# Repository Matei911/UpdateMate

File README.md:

# UpdateMate

**UpdateMate** is an open-source, low-power ePaper tablet designed for tinkerers, developers, and DIY enthusiasts.  
Built around the ESP32 microcontroller, it offers a customizable platform for displaying relevant, distraction-free information — from weather forecasts and calendar events to news, sensor data, and more.

## Preview

<table>
  <tr>
    <td align="center"><br/><sub>3D View of Tablet</sub></td>
    <td align="center"><br/><sub>3D View of PCB</sub></td>
  </tr>
  <tr>
    <td align="center"><br/><sub>Exploded View (Top)</sub></td>
    <td align="center"><br/><sub>Exploded View (Bottom)</sub></td>
  </tr>
</table>

## Features

- 🖥️ 7.5-inch black-and-white ePaper display from Waveshare  
- ⚡ Low power consumption with deep sleep support  
- 🧩 Rich peripheral support: sensors, SD card, RTC, fuel gauge, and more  
- 🔧 Designed for customization: easily add your own widgets, components, or software

## Ideal for

- 📖 eBook and tablet replacements  
- 🏡 Smart home dashboards  
- 🌦️ Always-on weather/news displays  
- 📅 Personal productivity boards  
- 📡 IoT project front-ends  
- 🧪 Educational embedded systems kits

## Bill of Materials (BoM)

The main components in the tablet

| Component               | Interface | Description                                 | Link |
|------------------------|-----------|---------------------------------------------|------|
| **ESP32-C6-WROOM-1-N4**| MCU       | Main microcontroller                        | [Mouser](https://eu.mouser.com/ProductDetail/Espressif-Systems/ESP32-C6-WROOM-1-N4?qs=8Wlm6%252BaMh8R1JRAtXlt87w%3D%3D) |
| **7.5" Waveshare ePaper** | SPI    | Black-and-white e-paper display             | [Waveshare](https://www.waveshare.com/7.5inch-e-paper.htm) |
| **MicroSD Card Socket** | SPI       | For storage and data logging                | [TME](https://www.tme.eu/ro/details/mcc-sdmicro/conectori-pentru-cartele/attend/112a-taar-r03/?utm_source=google&utm_medium=cpc&utm_campaign=RUMUNIA%20%5BP%5D%5BDC%5D&gad_source=1&gad_campaignid=8175080604&gbraid=0AAAAADyylhKvBZhJjt9PiCTA7ccHCAagN&gclid=Cj0KCQjw-NfDBhDyARIsAD-ILeD5bqtRTQDJJ5KzH339OMhsTZl5OwnY6A_-zTqHLYSh2y26Atg0Cr8aAshjEALw_wcB&gclsrc=aw.ds) |
| **W25Q512JVEIQ NOR Flash** | SPI  | 64 MB external flash memory                 | [Mouser](https://eu.mouser.com/ProductDetail/Winbond/W25Q512JVEIQ?qs=l7cgNqFNU1jw6svr3at6tA%3D%3D) |
| **MAX17048 Fuel Gauge** | I2C       | Battery voltage and state-of-charge monitor | [Mouser](https://eu.mouser.com/ProductDetail/Analog-Devices-Maxim-Integrated/MAX17048G%2bT10?qs=D7PJwyCwLAoGnnn8jEPRBQ%3D%3D) |
| **BME680 Sensor Board** | I2C       | Environmental sensor (temp, humidity, gas)  | [Mouser](https://eu.mouser.com/ProductDetail/Bosch-Sensortec/BME680-Shuttle-Board-3.0?qs=Wj%2FVkw3K%252BMABg5lm5143Ww%3D%3D) |
| **DS3231SN RTC**        | I2C       | Real-time clock with temperature compensation | [Mouser](https://eu.mouser.com/ProductDetail/Analog-Devices-Maxim-Integrated/DS3231SN?qs=1eQvB6Dk1vhUlr8%2FOrV0Fw%3D%3D&utm_id=20109199409&utm_source=google&utm_medium=cpc&utm_marketing_tactic=emeacorp&gad_source=1&gad_campaignid=20109199409&gbraid=0AAAAADn_wf2OPp6JmRENVY2T7SRbqdMYH&gclid=Cj0KCQjw-NfDBhDyARIsAD-ILeBzHcIxR8KDbRAJnh_ZM7th9YkG_cXsf5fStQOxZy3EcUWmKn77gJcaAmQ9EALw_wcB) |

## Gallery

Pictures with the features already implemented on the tablet.

<table>
  <tr>
    <td align="center">
      <br/>
      <sub>Main Page View</sub>
    </td>
    <td align="center">
      <br/>
      <sub>eBook Page View</sub>
    </td>
    <td align="center">
      <br/>
      <sub>Stock Page View</sub>
    </td>
  </tr>
  <tr>
    <td align="center">
      <br/>
      <sub>News Page View</sub>
    </td>
    <td align="center">
      <br/>
      <sub>App Launcher View</sub>
    </td>
    <td align="center">
      <br/>
      <sub>PCB inside case</sub>
    </td>
  </tr>
</table>

## Contents

The repository is structured into two main sections:

### `/hardware`
- Autodesk Fusion 360 design files for the custom PCB  
- 3D model files for the full tablet case, including STL/STEP formats for printing or editing  
- Schematics and layout files for manufacturing the board

### `/software`
- Arduino sketches for individual components (e.g. display, sensors, Wi-Fi, etc.) for testing  
- Full firmware implementation for the UpdateMate tablet, enabling all features shown in the gallery (weather, news, stocks, calendar, eBooks)

**Enjoy tinkering!**

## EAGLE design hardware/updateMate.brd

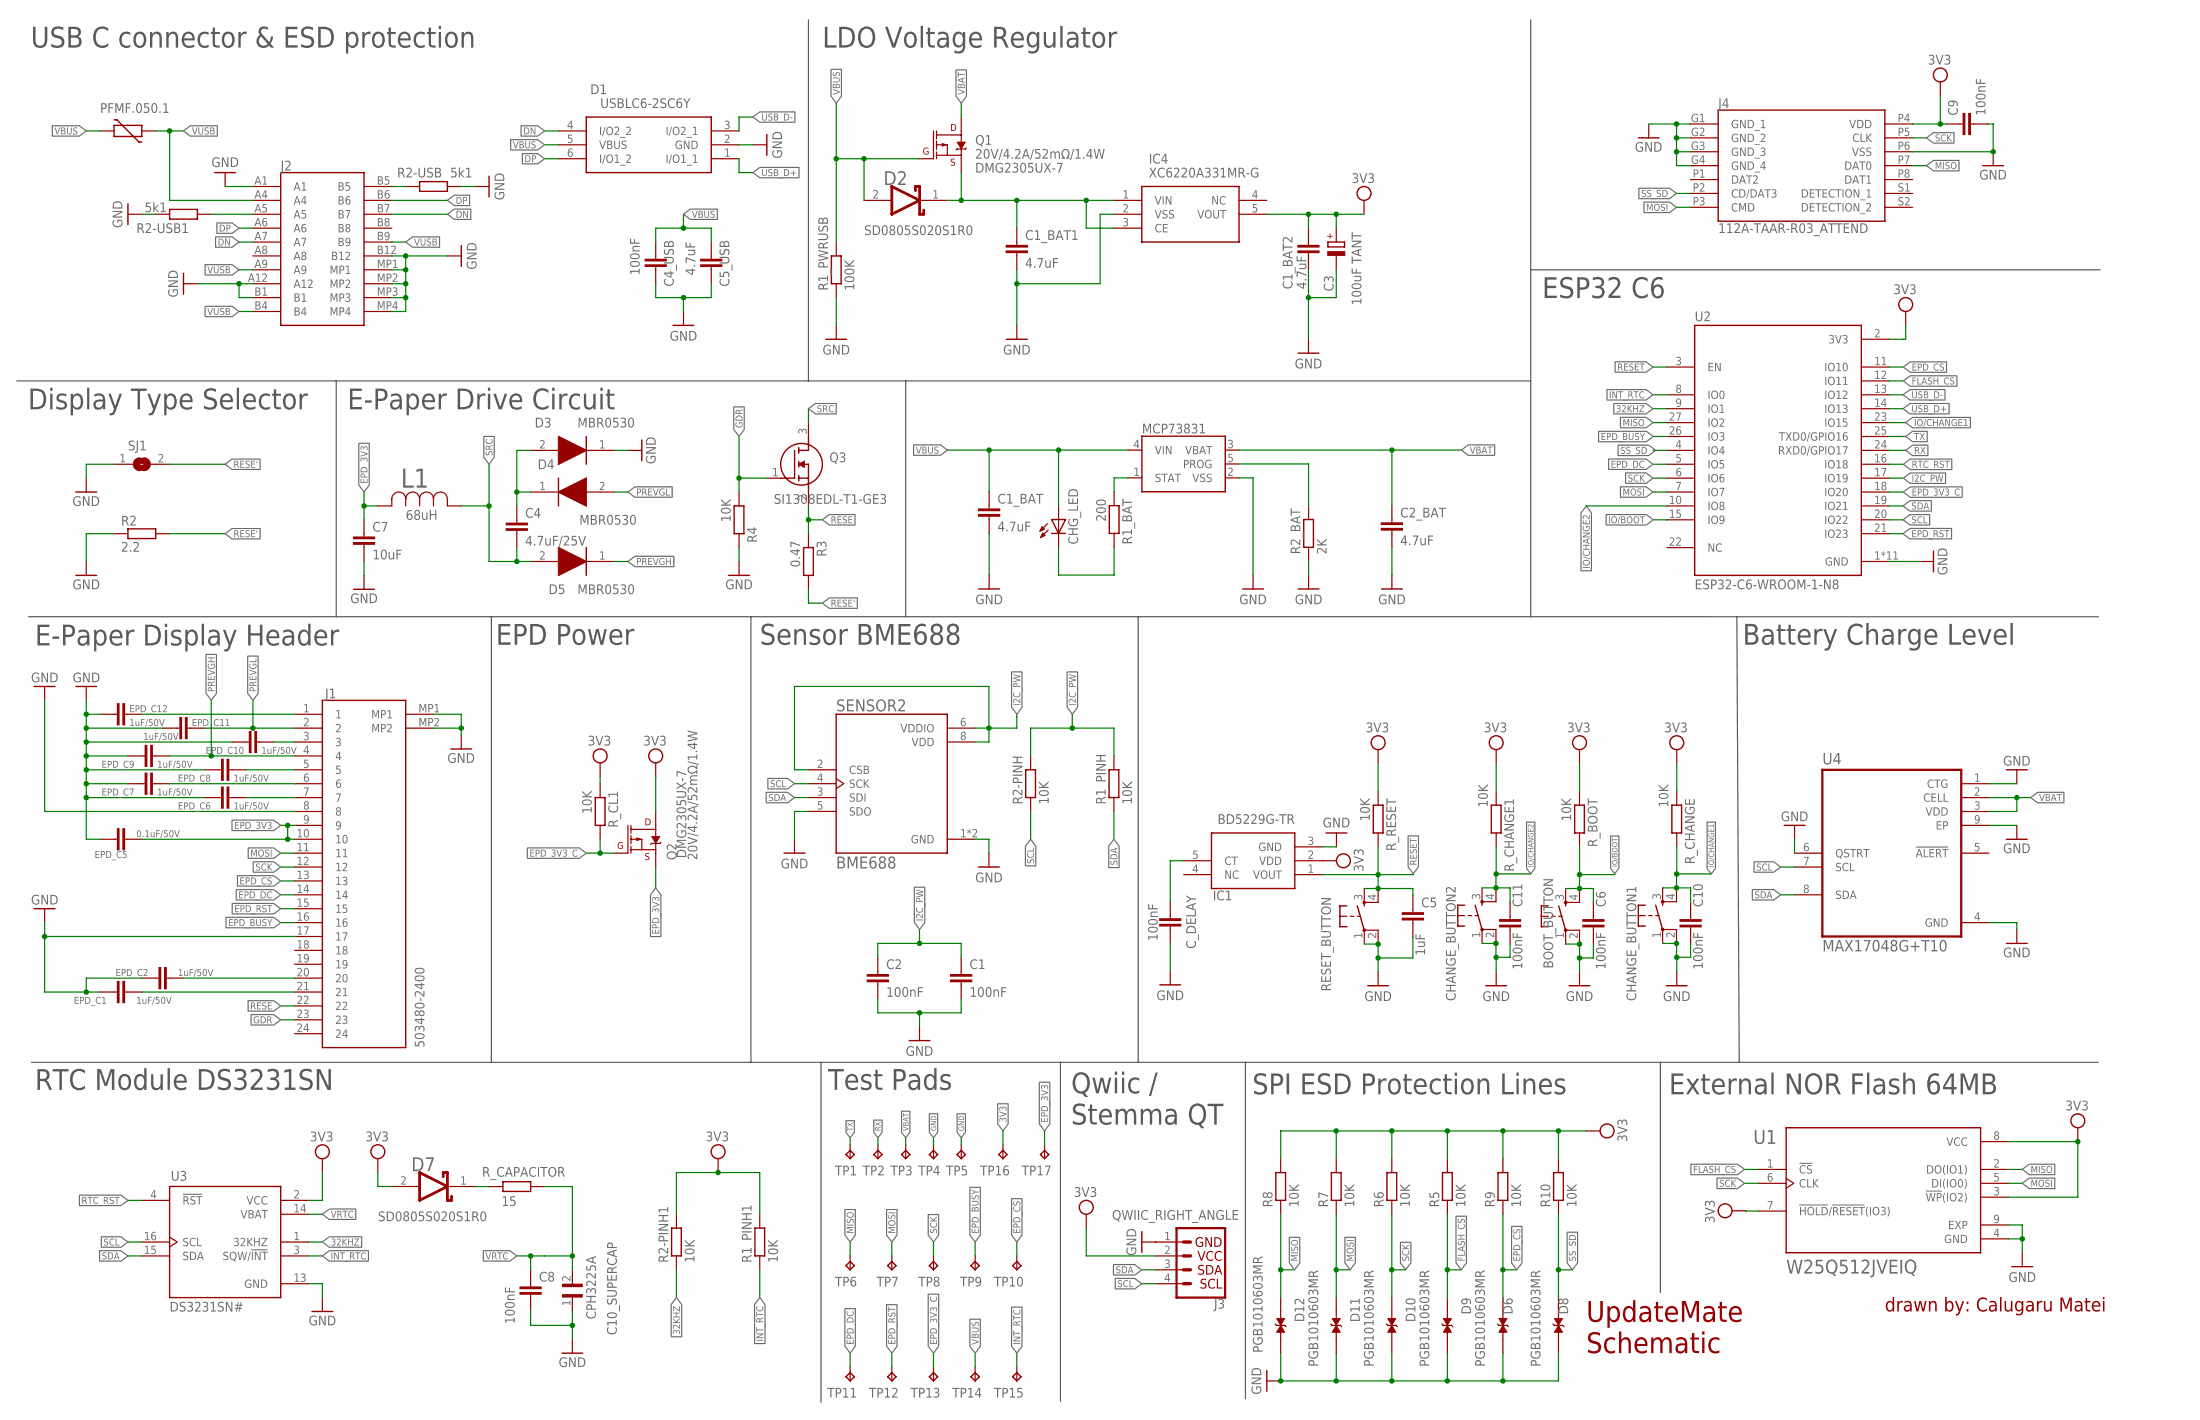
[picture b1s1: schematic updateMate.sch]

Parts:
BOOT_BUTTON: BUTTON_CUSYOMV1; MYBUTTON
C1, C2, C4_USB, C6, C8, C10, C11: 100nF; ESP32_WROVER_EAGLE-LTSPICE_C0402
C1_BAT, C1_BAT1, C1_BAT2, C2_BAT, C5_USB: 4.7uF; ESP32_WROVER_EAGLE-LTSPICE_C0402
C3: 100uF TANT; RCL_CT3528
C4: 4.7uF/25V; ESP32_WROVER_EAGLE-LTSPICE_C0402
C5: 1uF; ESP32_WROVER_EAGLE-LTSPICE_C0402
C7: 10uF; ESP32_WROVER_EAGLE-LTSPICE_C0402
C9: 100nF; EAGLE-LTSPICE_C0402
C10_SUPERCAP: CPH3225A; CAPCP3225X100N
CHANGE_BUTTON1, CHANGE_BUTTON2: BUTTON_CUSYOMV1; MYBUTTON
CHG_LED: ADAFRUIT_LEDCHIP-LED0603; ADAFRUIT_CHIP-LED0603
C_DELAY: 100nF; ESP32_WROVER_EAGLE-LTSPICE_C0402
D1: USBLC6-2SC6Y; SOT95P280X145-6N
D2: ESP32_WROVER_AVX---SD0805S020S1R0_AVX_SD0805S020S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; ESP32_WROVER_AVX---SD0805S020S1R0_AVX_SD0805S020S1R0_0
D3, D4, D5: MBR0530; SOD3716X135N
D6, D8, D9, D10, D11, D12: PGB1010603MR; DIOC1608X36N
D7: SD0805S020S1R0; ESP32_WROVER_AVX---SD0805S020S1R0_AVX_SD0805S020S1R0_0
EPD_C1, EPD_C2, EPD_C6, EPD_C7, EPD_C8, EPD_C9, EPD_C10, EPD_C11, EPD_C12: 1uF/50V; ESP32_WROVER_EAGLE-LTSPICE_C0402
EPD_C5: 0.1uF/50V; ESP32_WROVER_EAGLE-LTSPICE_C0402
IC1: BD5229G-TR; SOT95P280X125-5N
IC4: XC6220A331MR-G; SOT95P280X120-5N
J1: 503480-2400; 5034802400
J2: SAMACSYS_PARTS_USB4110-GF-A; SAMACSYS_PARTS_USB4110GFA
J3: QWIIC_RIGHT_ANGLE; JST04_1MM_RA
J4: 112A-TAAR-R03_ATTEND; 112ATAARR03ATTEND
L1: 68uH; IND_4828-WE-TPC_WRE
MCP73831: ESP32_WROVER_SPARKFUN-IC-POWER_MCP73831; ESP32_WROVER_SPARKFUN-IC-POWER_SOT23-5
PFMF.050.1: ESP32C6_VARISTORCN1812; ESP32C6_VARISTOR_CT/CN1812
Q1, Q2: 20V/4.2A/52mΩ/1.4W; ESP32_WROVER_SPARKFUN-DISCRETESEMI_SOT23-3
Q3: SI1308EDL-T1-GE3; SOT65P210X110-3N
R1_BAT: 200; ESP32_WROVER_EAGLE-LTSPICE_R0402
R1_PINH, R1_PINH1, R2-PINH, R2-PINH1, R4, R5, R6, R7, R8, R9, R10: 10K; ESP32_WROVER_EAGLE-LTSPICE_R0402
R1_PWRUSB: 100K; ESP32_WROVER_EAGLE-LTSPICE_R0402
R2: 2.2; ESP32_WROVER_EAGLE-LTSPICE_R0402
R2-USB, R2-USB1: 5k1; ESP32_WROVER_EAGLE-LTSPICE_R0402
R2_BAT: 2K; ESP32_WROVER_EAGLE-LTSPICE_R0402
R3: 0.47; ESP32_WROVER_EAGLE-LTSPICE_R0402
RESET_BUTTON: BUTTON_CUSYOMV1; MYBUTTON
R_BOOT: 10K; ESP32_WROVER_EAGLE-LTSPICE_R0402
R_CAPACITOR: 15; ESP32_WROVER_EAGLE-LTSPICE_R0402
R_CHANGE, R_CHANGE1: 10K; ESP32_WROVER_EAGLE-LTSPICE_R0402
R_CL1: 10K; ESP32_WROVER_EAGLE-LTSPICE_R0402
R_RESET: 10K; ESP32_WROVER_EAGLE-LTSPICE_R0402
SENSOR2: BME688; ESP32_WROVER_BME680_PSON80P300X300X100-8N
SJ1: SJ
TP1, TP2, TP3, TP4, TP5, TP6, TP7, TP8, TP9, TP10, TP11, TP12, TP13, TP14, TP15, TP16, TP17: TPTP20R; TP20R
U1: W25Q512JVEIQ; SON127P600X800X80-9N
U2: ESP32-C6-WROOM-1-N8; XCVR_ESP32-C6-WROOM-1-N8
U3: DS3231SN#; SOIC127P1032X265-16N
U4: MAX17048G+T10; SON50P200X200X80-9N

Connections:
3V3: C1_BAT2.1, C3.+, C9.1, D7.2 (ANODE), IC1.2 (VDD), IC4.5 (VOUT), J3.2, J4.P4 (VDD), Q2.3 (D), R1_PINH1.2, R2-PINH1.2, R5.2, R6.2, R7.2, R8.2, R9.2, R10.2, R_BOOT.1, R_CHANGE.1, R_CHANGE1.1, R_CL1.1, R_RESET.1, TP16.TP, U1.3 (!WP!(IO2)), U1.7 (!HOLD!/!RESET!(IO3)), U1.8 (VCC), U2.2 (3V3), U3.2 (VCC)
32KHZ: R2-PINH1.1, U2.9 (IO1), U3.1 (32KHZ)
DN: D1.4 (I/O2_2), J2.A7, J2.B7
DP: D1.6 (I/O1_2), J2.A6, J2.B6
EPD_3V3: C7.1, EPD_C5.1, J1.9, J1.10, L1.2, Q2.2 (S), TP17.TP
EPD_3V3_C: Q2.1 (G), R_CL1.2, TP13.TP, U2.18 (IO20)
EPD_BUSY: J1.16, TP9.TP, U2.26 (IO3)
EPD_CS: D6.1, J1.13, R9.1, TP10.TP, U2.11 (IO10)
EPD_DC: J1.14, TP11.TP, U2.5 (IO5)
EPD_RST: J1.15, TP12.TP, U2.21 (IO23)
FLASH_CS: D9.1, R5.1, U1.1 (!CS), U2.12 (IO11)
GDR: J1.23, Q3.1 (G), R4.1
GND: BOOT_BUTTON.1, BOOT_BUTTON.2, C1.2, C1_BAT.2, C1_BAT1.2, C1_BAT2.2, C2.2, C2_BAT.2, C3.-, C4_USB.2, C5.2, C5_USB.2, C6.2, C7.2, C8.2, C9.2, C10.2, C10_SUPERCAP.1, C11.2, CHANGE_BUTTON1.1, CHANGE_BUTTON1.2, CHANGE_BUTTON2.1, CHANGE_BUTTON2.2, C_DELAY.2, D1.2 (GND), D3.1 (K), D6.2, D8.2, D9.2, D10.2, D11.2, D12.2, EPD_C1.2, EPD_C2.2, EPD_C5.2, EPD_C6.2, EPD_C7.2, EPD_C8.2, EPD_C9.2, EPD_C10.2, EPD_C11.2, EPD_C12.2, IC1.3 (GND), IC4.2 (VSS), J1.8, J1.17, J1.MP1, J1.MP2, J2.A1, J2.A12, J2.B1, J2.B12, J2.MP1, J2.MP2, J2.MP3, J2.MP4, J3.1, J4.G1 (GND_1), J4.G2 (GND_2), J4.G3 (GND_3), J4.G4 (GND_4), J4.P6 (VSS), MCP73831.2 (VSS), R1_PWRUSB.1, R2.1, R2-USB.2, R2-USB1.1, R2_BAT.1, R4.2, RESET_BUTTON.1, RESET_BUTTON.2, SENSOR2.1 (GND), SENSOR2.5 (SDO), SENSOR2.7 (GND), SJ1.1, TP4.TP, TP5.TP, U1.4 (GND), U1.9 (EXP), U2.1 (GND), U2.28 (GND), U2.29_1 (GND), U2.29_2 (GND), U2.29_3 (GND), U2.29_4 (GND), U2.29_5 (GND), U2.29_6 (GND), U2.29_7 (GND), U2.29_8 (GND), U2.29_9 (GND), U3.13 (GND), U4.1 (CTG), U4.4 (GND), U4.6 (QSTRT), U4.9 (EP)
I2C_PW: C1.1, C2.1, R1_PINH.2, R2-PINH.2, SENSOR2.2 (CSB), SENSOR2.6 (VDDIO), SENSOR2.8 (VDD), U2.17 (IO19)
INT_RTC: R1_PINH1.1, TP15.TP, U2.8 (IO0), U3.3 (SQW/!INT)
IO/BOOT: BOOT_BUTTON.3, BOOT_BUTTON.4, C6.1, R_BOOT.2, U2.15 (IO9)
IO/CHANGE1: C10.1, CHANGE_BUTTON1.3, CHANGE_BUTTON1.4, R_CHANGE.2, U2.23 (IO15)
IO/CHANGE2: C11.1, CHANGE_BUTTON2.3, CHANGE_BUTTON2.4, R_CHANGE1.2, U2.10 (IO8)
MISO: D12.1, J4.P7 (DAT0), R8.1, TP6.TP, U1.2 (DO(IO1)), U2.27 (IO2)
MOSI: D11.1, J1.11, J4.P3 (CMD), R7.1, TP7.TP, U1.5 (DI(IO0)), U2.7 (IO7)
unnamed: J2.B5, R2-USB.1
unnamed: C_DELAY.1, IC1.5 (CT)
unnamed: C1_BAT1.1, D2.1 (CATHODE), IC4.1 (VIN), IC4.3 (CE), Q1.2 (S)
unnamed: J2.A5, R2-USB1.2
unnamed: D7.1 (CATHODE), R_CAPACITOR.2
unnamed: EPD_C1.1, J1.21
unnamed: EPD_C2.1, J1.20
unnamed: C4.1, D3.2 (A), D4.1 (K)
unnamed: MCP73831.5 (PROG), R2_BAT.2
unnamed: MCP73831.1 (STAT), R1_BAT.1
unnamed: CHG_LED.C, R1_BAT.2
unnamed: EPD_C6.1, J1.7
unnamed: EPD_C7.1, J1.6
unnamed: EPD_C8.1, J1.5
unnamed: EPD_C10.1, J1.3
unnamed: EPD_C12.1, J1.1
PREVGH: D5.1 (K), EPD_C9.1, J1.4
PREVGL: D4.2 (A), EPD_C11.1, J1.2
RESE: J1.22, Q3.2 (S), R3.1
RESE': R2.2, R3.2, SJ1.2
RESET: C5.1, IC1.1 (VOUT), RESET_BUTTON.3, RESET_BUTTON.4, R_RESET.2, U2.3 (EN)
RTC_RST: U2.16 (IO18), U3.4 (!RST)
RX: TP2.TP, U2.24 (RXD0/GPIO17)
SCK: D10.1, J1.12, J4.P5 (CLK), R6.1, TP8.TP, U1.6 (CLK), U2.6 (IO6)
SCL: J3.4, R2-PINH.1, SENSOR2.4 (SCK), U2.20 (IO22), U3.16 (SCL), U4.7 (SCL)
SDA: J3.3, R1_PINH.1, SENSOR2.3 (SDI), U2.19 (IO21), U3.15 (SDA), U4.8 (SDA)
SRC: C4.2, D5.2 (A), L1.1, Q3.3 (D)
SS_SD: D8.1, J4.P2 (CD/DAT3), R10.1, U2.4 (IO4)
TX: TP1.TP, U2.25 (TXD0/GPIO16)
USB_D+: D1.1 (I/O1_1), U2.14 (IO13)
USB_D-: D1.3 (I/O2_1), U2.13 (IO12)
VBAT: C2_BAT.1, MCP73831.3 (VBAT), Q1.3 (D), TP3.TP, U4.2 (CELL), U4.3 (VDD)
VBUS: C1_BAT.1, C4_USB.1, C5_USB.1, CHG_LED.A, D1.5 (VBUS), D2.2 (ANODE), MCP73831.4 (VIN), PFMF.050.1.1, Q1.1 (G), R1_PWRUSB.2, TP14.TP
VRTC: C8.1, C10_SUPERCAP.2, R_CAPACITOR.1, U3.14 (VBAT)
VUSB: J2.A4, J2.A9, J2.B4, J2.B9, PFMF.050.1.2

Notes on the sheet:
USB C connector & ESD protection
LDO Voltage Regulator
Battery Charge Level
Sensor BME688
ESP32 C6
Qwiic / Stemma QT
External NOR Flash 64MB
E-Paper Display Header
Display Type Selector
E-Paper Drive Circuit
SPI ESD Protection Lines
EPD Power
RTC Module DS3231SN
Test Pads
SD0805S020S1R0
68uH
drawn by: Calugaru Matei
UpdateMate Schematic
DMG2305UX-7

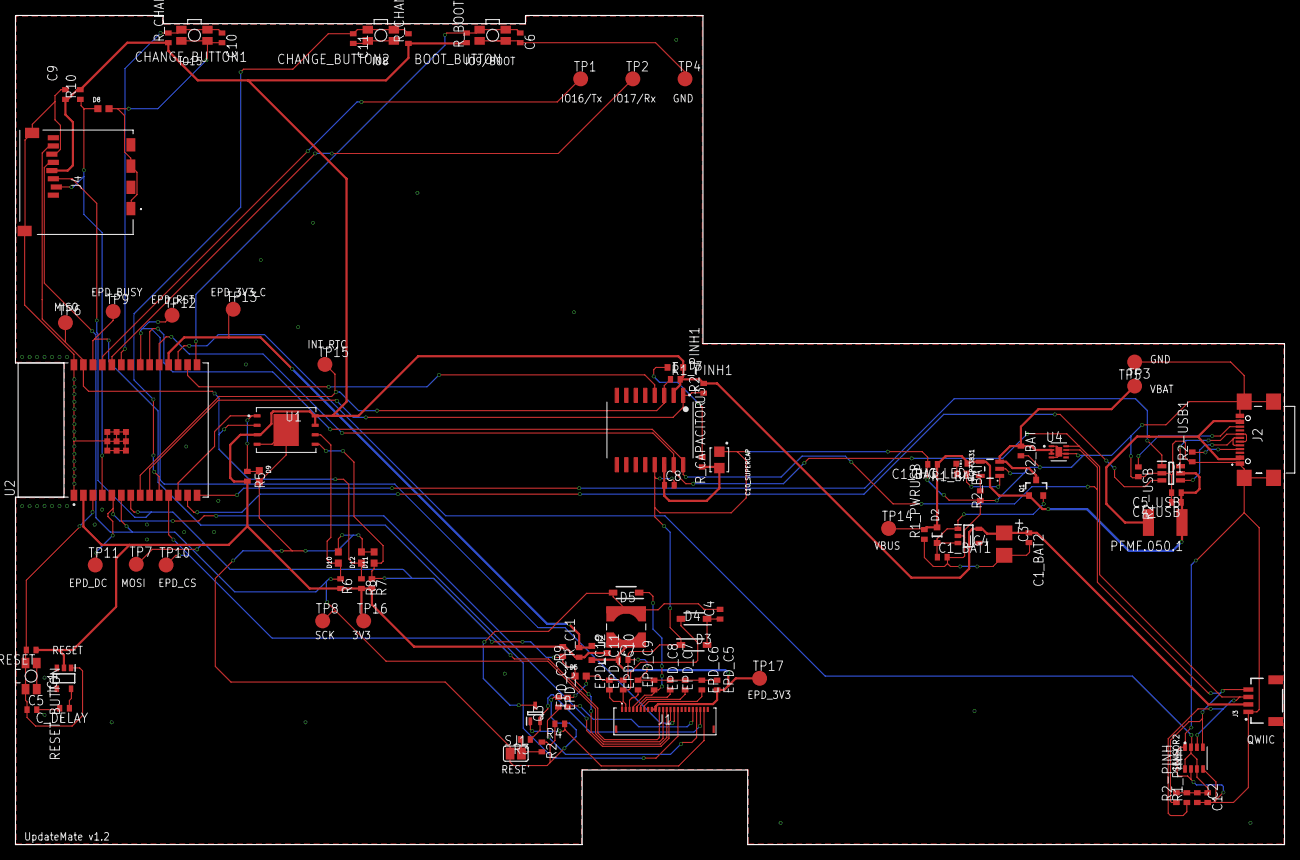
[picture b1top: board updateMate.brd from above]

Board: 2 copper layers, 170.2 x 111.2 mm, 105 parts (0 on the bottom side), 55 nets.

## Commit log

2025-07-14 Create assets
2025-07-15 Adding gallery pics
2025-07-15 Adding BOM
2025-07-15 Adding exploded pics
2025-07-15 Adding schematics and CAD Files
2025-07-15 Adding case 3D model
2025-07-15 Adding test codes for main components
2025-07-16 Adding UpdateMate first code version alongside other necessary files
2025-07-16 Fix README

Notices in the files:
parts and their libraries:
COPYRIGHT: Copyright (C) 2024 Ultra Librarian. All rights reserved.
